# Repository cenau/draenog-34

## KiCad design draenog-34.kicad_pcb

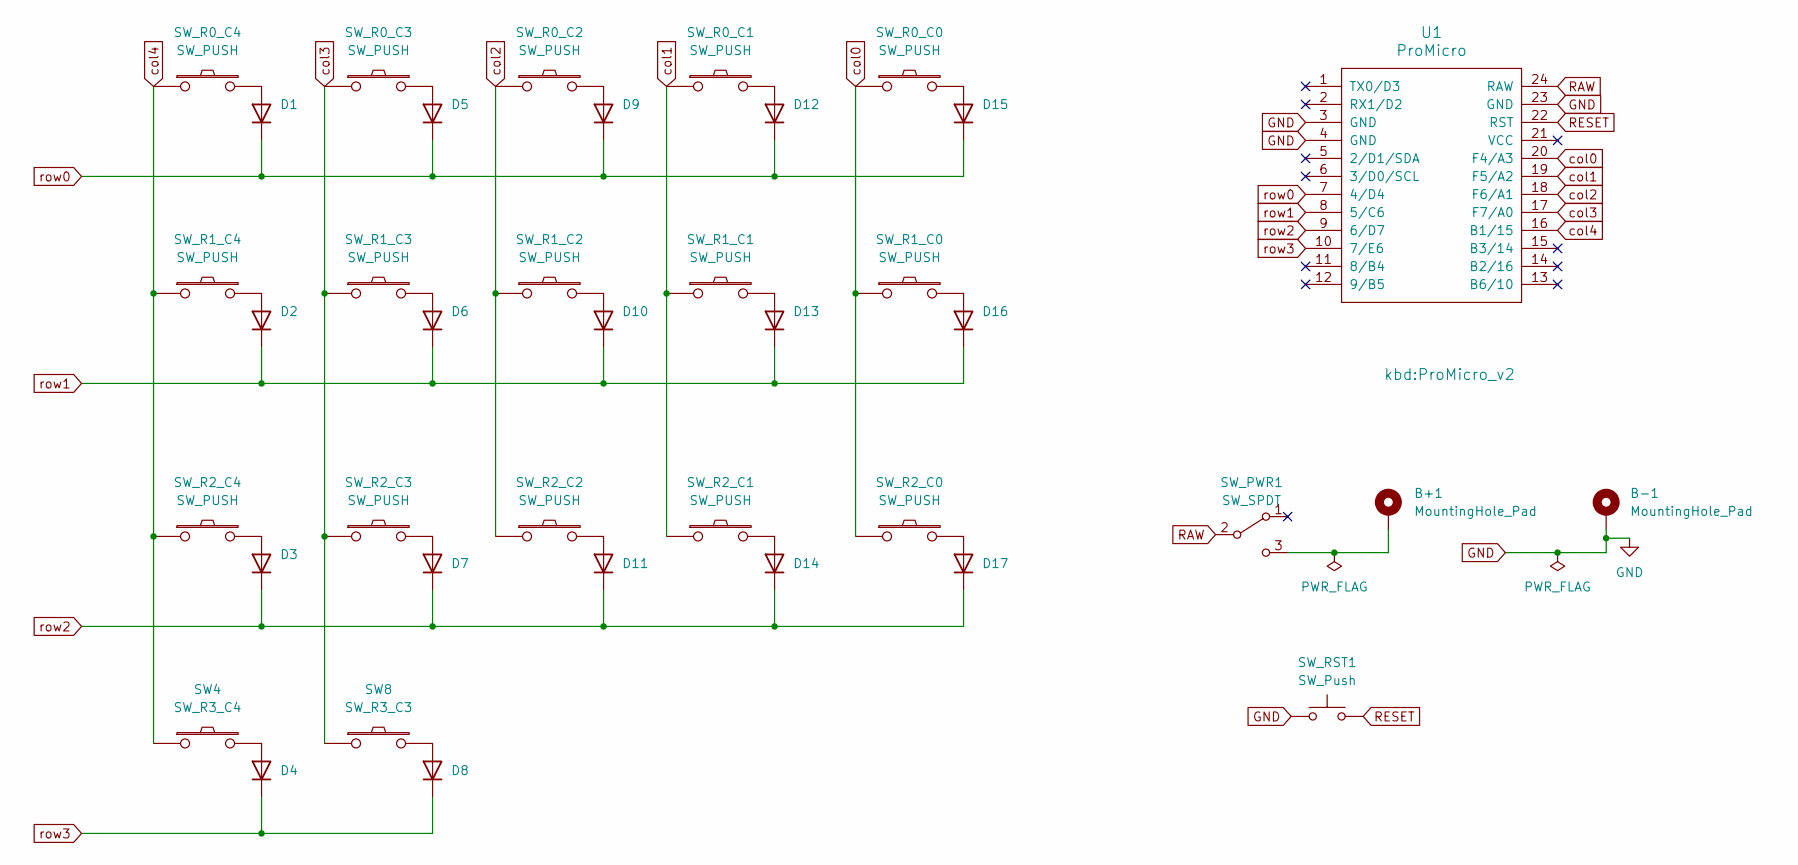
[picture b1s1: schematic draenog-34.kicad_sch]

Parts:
B+1: MountingHole_Pad; 1pin_conn
B-1: MountingHole_Pad; 1pin_conn
D1, D2, D3, D4, D5, D6, D7, D8, D9, D10, D11, D12, D13, D14, D15, D16, D17: 1N4148W; D3_SMD
SW4: SW_R3_C4; Kailh_socket_PG1350_reversible
SW8: SW_R3_C3; Kailh_socket_PG1350_reversible
SW_PWR1: SW_SPDT; SW_MSK12C02-HB
SW_R0_C0, SW_R0_C1, SW_R0_C2, SW_R0_C3, SW_R0_C4, SW_R1_C0, SW_R1_C1, SW_R1_C2, SW_R1_C3, SW_R1_C4, SW_R2_C0, SW_R2_C1, SW_R2_C2, SW_R2_C3, SW_R2_C4: SW_PUSH; Kailh_socket_PG1350_reversible
SW_RST1: SW_Push; ResetSW
U1: ProMicro; ProMicro_v2

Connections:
GND: B-1.1, SW_RST1.1, U1.3 (GND), U1.4 (GND), U1.23 (GND)
unnamed: D1.2 (A), SW_R0_C4.2
unnamed: D2.2 (A), SW_R1_C4.2
unnamed: D3.2 (A), SW_R2_C4.2
unnamed: D4.2 (A), SW4.2
unnamed: D5.2 (A), SW_R0_C3.2
unnamed: D6.2 (A), SW_R1_C3.2
unnamed: D7.2 (A), SW_R2_C3.2
unnamed: D8.2 (A), SW8.2
unnamed: D9.2 (A), SW_R0_C2.2
unnamed: D10.2 (A), SW_R1_C2.2
unnamed: D11.2 (A), SW_R2_C2.2
unnamed: D12.2 (A), SW_R0_C1.2
unnamed: D13.2 (A), SW_R1_C1.2
unnamed: D14.2 (A), SW_R2_C1.2
unnamed: D15.2 (A), SW_R0_C0.2
unnamed: D16.2 (A), SW_R1_C0.2
unnamed: D17.2 (A), SW_R2_C0.2
unnamed: B+1.1, SW_PWR1.3 (C)
RAW: SW_PWR1.2 (B), U1.24 (RAW)
RESET: SW_RST1.2, U1.22 (RST)
col0: SW_R0_C0.1, SW_R1_C0.1, SW_R2_C0.1, U1.20 (F4/A3)
col1: SW_R0_C1.1, SW_R1_C1.1, SW_R2_C1.1, U1.19 (F5/A2)
col2: SW_R0_C2.1, SW_R1_C2.1, SW_R2_C2.1, U1.18 (F6/A1)
col3: SW8.1, SW_R0_C3.1, SW_R1_C3.1, SW_R2_C3.1, U1.17 (F7/A0)
col4: SW4.1, SW_R0_C4.1, SW_R1_C4.1, SW_R2_C4.1, U1.16 (B1/15)
row0: D1.1 (K), D5.1 (K), D9.1 (K), D12.1 (K), D15.1 (K), U1.7 (4/D4)
row1: D2.1 (K), D6.1 (K), D10.1 (K), D13.1 (K), D16.1 (K), U1.8 (5/C6)
row2: D3.1 (K), D7.1 (K), D11.1 (K), D14.1 (K), D17.1 (K), U1.9 (6/D7)
row3: D4.1 (K), D8.1 (K), U1.10 (7/E6)

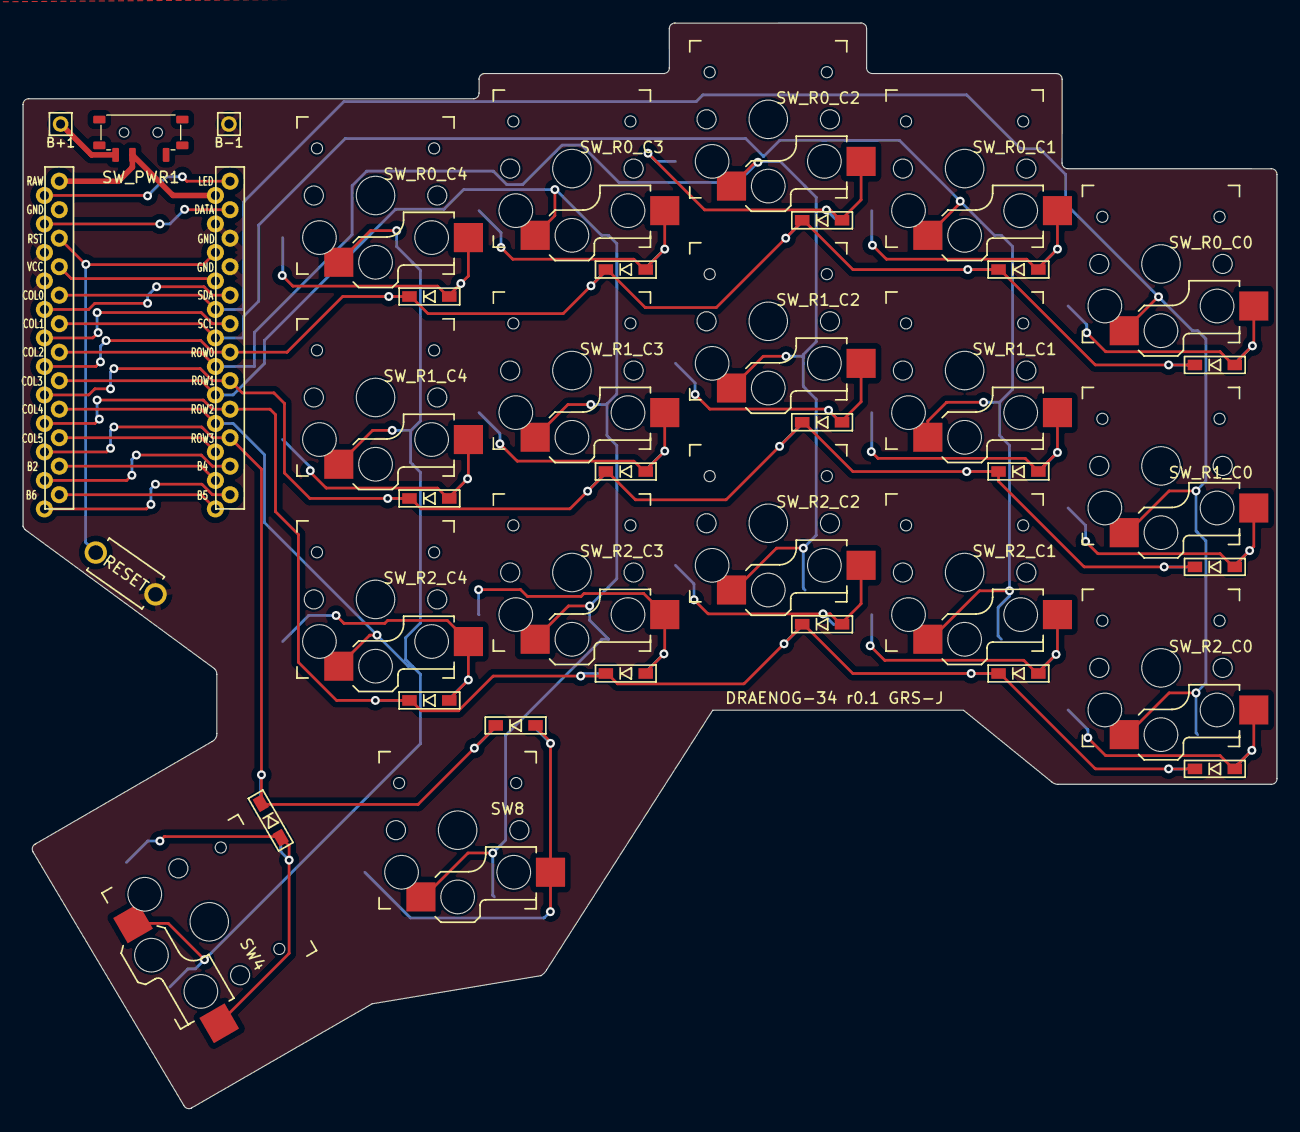
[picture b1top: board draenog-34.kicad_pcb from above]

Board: 2 copper layers, 111.8 x 96.8 mm, 39 parts (0 on the bottom side), 30 nets.
